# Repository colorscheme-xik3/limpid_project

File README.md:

## Overview

The Limpid Project is an Internet of Things (IoT) initiative aimed at monitoring water quality. The project utilizes IoT devices to collect data on various water parameters, providing valuable insights into the quality of water in different environments.

## Features

- Real-time monitoring of water quality parameters.
- Data collection for pH levels, temperature, dissolved oxygen, and more.
- User-friendly interface for visualizing and analyzing collected data.
- Alerts and notifications for abnormal water quality conditions.
- Historical data storage for trend analysis using dashboard.

## Technologies Used

- **Hardware:** [ESP-32 DEVKITV4]
- **Software:** [C, kotlin, Angular, python]
- **Design:** [kicad]

## Varuna5 PCB

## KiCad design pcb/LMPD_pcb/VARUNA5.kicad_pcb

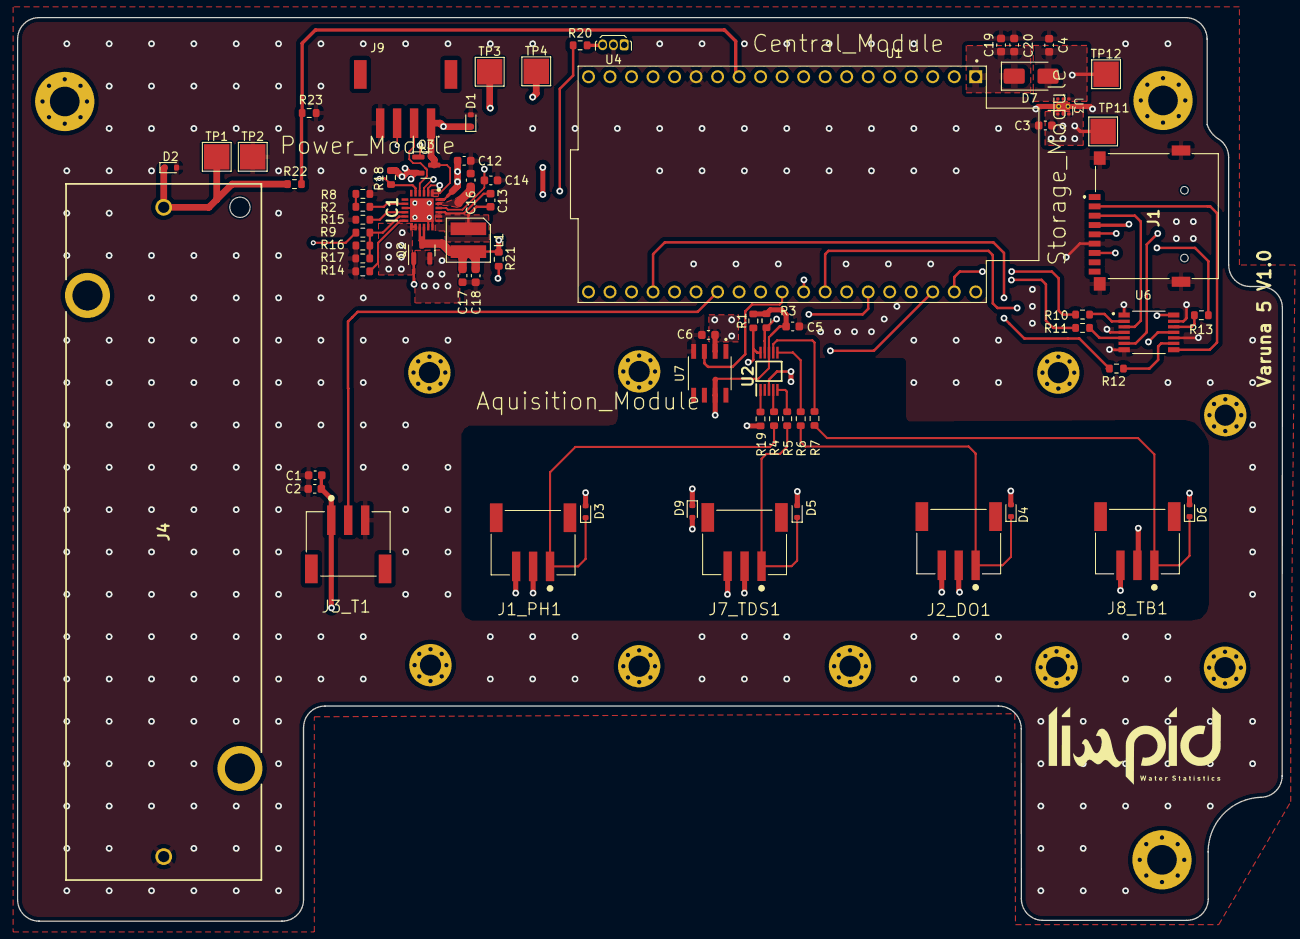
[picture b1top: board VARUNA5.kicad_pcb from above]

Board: 4 copper layers, 149.3 x 106.7 mm, 69 parts (0 on the bottom side), 50 nets.

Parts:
C1, C2, C3, C4, C18, C19: 100n; C_0603_1608Metric
C5: 4.7u; C_0603_1608Metric
C6: 2.2u; C_0603_1608Metric
C12, C16: 10u; C_0603_1608Metric
C13: 47n; C_0603_1608Metric
C14: 4.7u - 10v; C_0603_1608Metric
C17, C20: 47u; C_0603_1608Metric
D1, D2, D3, D4, D5, D6, D9: TVS; D_SOD-523
D7: D_Schottky; D_SMA
IC1: BQ25616RTWT; QFN50P400X400X80-25N-D
J1: TF-15X15; TF15X15
J1_PH1, J2_DO1, J3_T1, J7_TDS1, J8_TB1: Conn_01x03; JST_S3B-PH-SM4-TB(LF)(SN)
J4: Batt; 1121
J9: Conn_01x04; JST_S4B-PH-SM4-TB
L1: 1uH; inductor_bourns_4x4
Q2: Q_PMOS_GSD; SOT-23
Q3: Q_NMOS_GSD; SOT-23
R1, R3, R14, R17, R18, R19, R21, R22, R23: 10k; R_0603_1608Metric
R2, R8: 120; R_0603_1608Metric
R4, R5, R6, R7, R10, R11, R12, R13, R15, R20: 330; R_0603_1608Metric
R9: 5.3k; R_0603_1608Metric
R16: 30k; R_0603_1608Metric
TP1, TP2, TP3, TP4, TP11, TP12: TestPoint_Pad_3.0x3.0mm
U1: ESP32-DEVKITC; MODULE_ESP32-DEVKITC
U2: ADS1115IDG; SOP50P490X110-10N
U3: LP5912-3.3DRV; asdasdasd
U4: AH3772-SA-7; TO-92Flat
U6: 74LVC125APW,118; IC_74LVC125APW,118
U7: REF196GSZ-REEL; SOIC127P600X175-8N

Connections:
/3.3V: C4.1, D7.2 (A), J1.4 (VDD), J8_TB1.2, TP12.1, U3.1 (OUT), U6.14 (VCC)
/BATT: D2.1 (A1), IC1.13 (BAT_1), IC1.14 (BAT_2), J4.2, R22.2, TP1.1
/BATT_CHECK: R22.1, R23.2, U1.12 (IO14)
/CTRL_GPIO: U1.29 (IO5), U7.3 (SHDN)
/DO_BREAK: D4.1 (A1), J2_DO1.1, R6.2
/DS_DATA: J3_T1.2, U1.26 (IO4)
/I2C_SCL: R1.2, U1.36 (IO22), U2.10 (SCL)
/I2C_SDA: R3.2, U1.33 (IO21), U2.9 (SDA)
/PH_BREAK: D3.1 (A1), J1_PH1.1, R4.2
/PRE_VCC: C17.1, C18.1, IC1.15 (SYS_1), IC1.16 (SYS_2), L1.2, Q2.3 (D), R21.2, U4.1 (IN)
/SDcard/CS_LLS: J1.2 (CD/DAT3), U6.8 (3Y)
/SDcard/DI_LLS: J1.3 (CMD), U6.3 (1Y)
/SDcard/DO_LLS: J1.7 (DAT0), R13.1
/SDcard/SCK_LLS: J1.5 (CLX), U6.6 (2Y)
/SPI_CS: R12.1, U1.23 (IO15)
/SPI_MISO: U1.31 (IO19), U6.11 (4Y)
/SPI_MOSI: R10.1, U1.37 (IO23)
/SPI_SCK: R11.1, U1.30 (IO18)
/STAT: IC1.5 (STAT), R18.2, U1.15 (IO13)
/TB_BREAK: D6.1 (A1), J8_TB1.1, R7.2
/TDS_BREAK: D5.1 (A1), J7_TDS1.1, R5.2
/USB5V: D1.1 (A1), IC1.1 (VAC), J9.1, Q3.3 (D), TP4.1
/USBD+: IC1.3 (D+), J9.3
/USBD-: IC1.4 (D-), J9.2
/VCC_RAW: C3.1, C6.1, Q2.2 (S), TP11.1, U3.4 (EN), U3.6 (IN), U7.2 (VIN)
/VREF3V3: C1.1, C2.1, C5.1, D9.1 (A1), J1_PH1.2, J2_DO1.2, J3_T1.1, J7_TDS1.2, R1.1, R3.1, U2.8 (VDD), U7.7 (VOUT)
/battery_module/ACDRV: IC1.2 (ACDRV), Q3.1 (G)
/battery_module/VIN: C12.1, IC1.24 (VBUS), Q3.2 (S), R18.1, TP3.1
GNDREF: C1.2, C2.2, C3.2, C4.2, C5.2, C6.2, C12.2, C14.2, C16.2, C17.2, C18.2, C19.2, C20.2, D1.2 (A2), D2.2 (A2), D3.2 (A2), D4.2 (A2), D5.2 (A2), D6.2 (A2), D9.2 (A2), IC1.9 (~CE), IC1.17 (GND_1), IC1.18 (GND_2), IC1.25 (EP), J1.6 (VSS), J1.MP1, J1.MP2, J1.MP3, J1.MP4, J1_PH1.3, J2_DO1.3, J3_T1.3, J4.1, J7_TDS1.3, J8_TB1.3, J9.4, R8.2, R14.2, R15.2, R16.1, R17.1, R19.2, R23.1, TP2.1, U1.14 (GND1), U2.3 (GND), U3.5 (GND), U3.7 (EP), U4.2, U6.1 (1~OE), U6.4 (2~OE), U6.7 (GND), U6.10 (3~OE), U6.13 (4~OE), U7.4 (GND)
unnamed: C19.1, C20.1, D7.1 (K), U1.1 (3V3)
unnamed: C13.1, IC1.21 (BTST)
unnamed: IC1.10 (ICHG), R15.1
unnamed: IC1.8 (ILIM), R2.1
unnamed: C16.1, IC1.23 (PMID)
unnamed: C14.1, IC1.22 (REGN), R9.1
unnamed: C13.2, IC1.19 (SW_1), IC1.20 (SW_2), L1.1
unnamed: IC1.11 (TS), R9.2, R16.2, R17.2
unnamed: IC1.12 (VSET), R14.1
unnamed: Q2.1 (G), R20.1, R21.1
unnamed: R2.2, R8.1
unnamed: R19.1, U2.1 (ADDR)
unnamed: R4.1, U2.4 (AIN0)
unnamed: R5.1, U2.5 (AIN1)
unnamed: R6.1, U2.6 (AIN2)
unnamed: R7.1, U2.7 (AIN3)
unnamed: R20.2, U4.3 (OUT)
unnamed: R10.2, U6.2 (1A)
unnamed: R11.2, U6.5 (2A)
unnamed: R12.2, U6.9 (3A)
unnamed: R13.2, U6.12 (4A)

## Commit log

2023-11-21 Readme commit
2023-11-21 images commit
2023-11-21 Readme logo added
2023-11-23 adding README for esp_code
2023-11-23 updating README for esp_code
2023-11-28 adding angular to dashboard
2023-11-29 login and wrapper added
2023-11-30 added dashboard and home components
2023-11-30 added dashboard and home components and ipma weather api
2023-12-01 bug fixes and logout button
2023-12-04 Trying to add apex.charts
2023-12-04 Adding apex.charts
2023-12-05 Adding cards to Water.component
2023-12-13 Adding firebase to cards
2023-12-15 Making windows responsive and adding Ipma temperature
2023-12-15 Adding Temperature animation on sidebar
2024-01-19 Adding realtimeGraph - incomplete
2024-03-04 Added graph updating with checkboxes
2024-03-06 Figuring selecting the graph days - TODO
2024-03-08 Figuring selecting the graph days - DONE
2024-03-15 adding ESP-IDF code folder
2024-03-20 adding handler functions and DS18B20 - Corrected ADS
2024-03-23 adding sdCard drive - TODO: Deep Sleep offline task
2024-04-03 Tests for the application
2024-04-25 Updated SDcard with .csv integration - Updated PowerMode - Updated Flush(Todo)
2024-04-29 Updated FLUSH
2024-05-14 Updated 1min Timing on APP
2024-05-14 PCB files added
2024-05-27 Added different Graph to dashboard
2024-05-31 Android code and System schematic
2024-05-31 Last details
2024-05-31 Readme
